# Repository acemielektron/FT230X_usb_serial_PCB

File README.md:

# FT230X_usb_serial_PCB
DIY FT230X based 3.3v usb serial pcb

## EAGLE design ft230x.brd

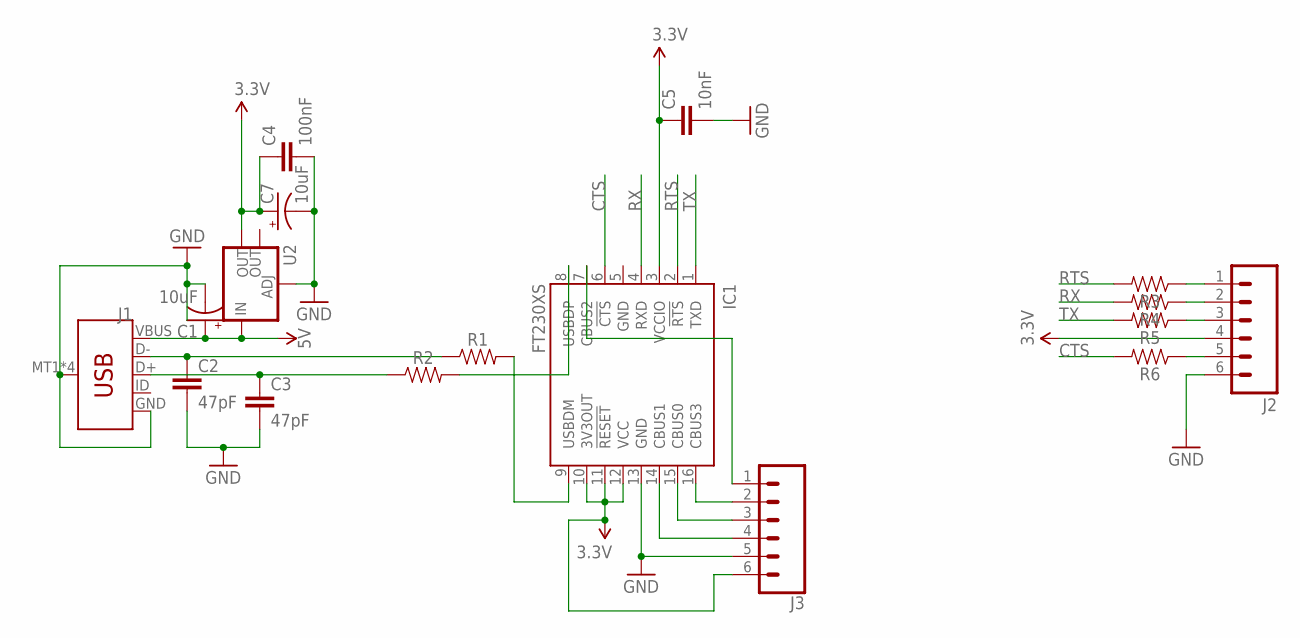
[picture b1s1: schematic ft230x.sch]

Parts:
C1, C7: 10uF; EIA3528
C2, C3: 47pF; 1206@1
C4: 100nF; 1206@1
C5: 10nF; 1206
IC1: FT230XS; SSOP16
J1: USB_MICRO-B_SMT; USB-MICROB
J2: M06SILK_FEMALE_PTH; 1X06@1
J3: CONN_06SILK_FEMALE_PTH; 1X06
R1, R2: 1206
R3, R4, R5, R6: 0805
U2: V_REG_LM1117SOT223; SOT223

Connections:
3.3V: C4.1, C5.1, C7.A (+), IC1.3 (VCCIO), IC1.10 (3V3OUT), IC1.11 (!RESET), IC1.12 (VCC), J2.4, J3.6, U2.2 (OUT)
5V: C1.A (+), J1.VBUS, U2.3 (IN)
CBUS0: IC1.15 (CBUS0), J3.3
CBUS1: IC1.14 (CBUS1), J3.4
CBUS2: IC1.7 (CBUS2), J3.1
CBUS3: IC1.16 (CBUS3), J3.2
CTS: IC1.6 (!CTS), R6.2
CTS-: J2.5, R6.1
D+: C3.1, J1.D+, R2.1
D-: C2.1, J1.D-, R1.1
GND: C1.C (-), C2.2, C3.2, C4.2, C5.2, C7.C (-), IC1.5 (GND), IC1.13 (GND), J1.GND, J1.MT1 (SHIELD), J1.MT2 (SHIELD), J1.P$1 (SHIELD), J1.P$2 (SHIELD), J2.6, J3.5, U2.1 (ADJ)
RD+: IC1.8 (USBDP), R2.2
RD-: IC1.9 (USBDM), R1.2
RTS: IC1.2 (!RTS), R3.2
RTS-: J2.1, R3.1
RX: IC1.4 (RXD), R4.2
RX-: J2.2, R4.1
TX: IC1.1 (TXD), R5.2
TX-: J2.3, R5.1

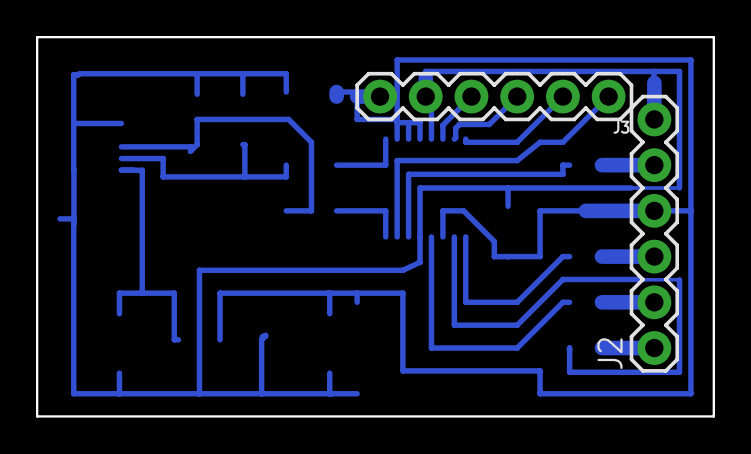
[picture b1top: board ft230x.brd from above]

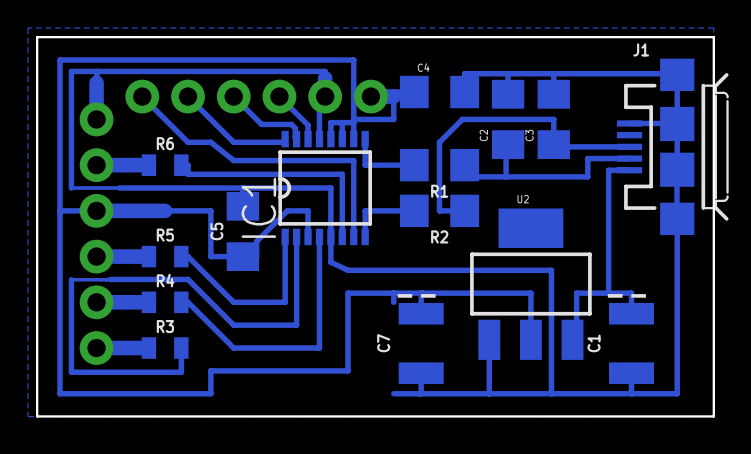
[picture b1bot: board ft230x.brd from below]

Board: 2 copper layers, 37.6 x 21.1 mm, 17 parts (15 on the bottom side), 19 nets.

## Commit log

2019-02-14 single sided pcb for FT230X

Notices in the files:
parts and their libraries:
SparkFun-Capacitors: Licensing: Creative Commons ShareAlike 4.0 International - https://creativecommons.org/licenses/by-sa/4.0
